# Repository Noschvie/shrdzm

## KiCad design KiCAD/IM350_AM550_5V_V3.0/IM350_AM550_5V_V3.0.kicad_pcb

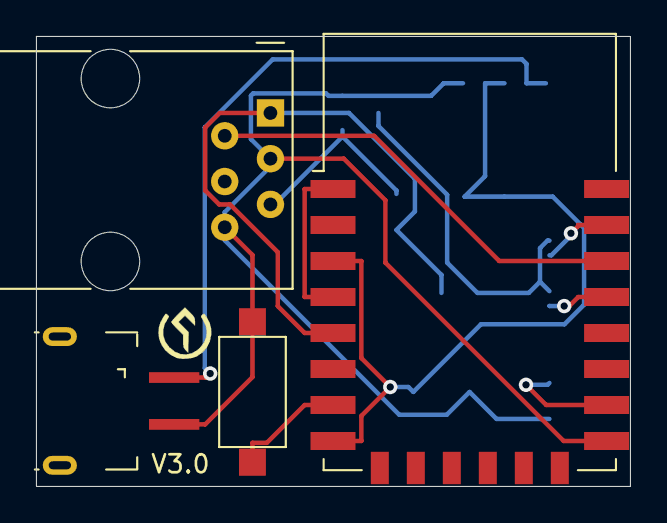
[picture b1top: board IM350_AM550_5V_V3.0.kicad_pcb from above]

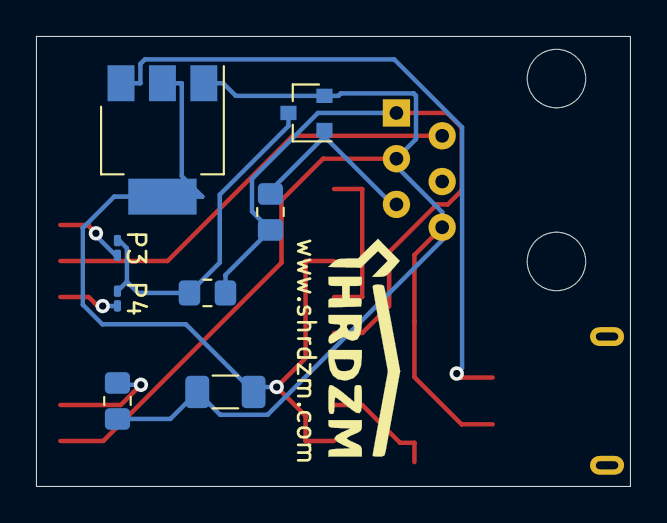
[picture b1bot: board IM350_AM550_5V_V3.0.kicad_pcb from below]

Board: 2 copper layers, 33.0 x 25.0 mm, 14 parts (9 on the bottom side), 12 nets.

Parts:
C1: 22uF; C_1206_3216Metric_Pad1.33x1.80mm_HandSolder
G1: LOGO; SHRDZM Symbol 3x3
G2: LOGO; SHRDZM 12x4
J1: USB_B_Micro_Power; USB_Micro-B_Power
J2: RJ12; RJ12_Amphenol_54601
P3, P4: 2.2k; R_0201_0603Metric_Pad0.64x0.40mm_HandSolder
Q1: BC847; SOT-23
R4, R6: 10k; R_0805_2012Metric_Pad1.20x1.40mm_HandSolder
R5: 2.2k; R_0805_2012Metric_Pad1.20x1.40mm_HandSolder
SW2: SW_Push; SW_SPST_CK_RS282G05A3
U1: AMS1117-3.3; SOT-223-3_TabPin2
U2: ESP-12F; ESP-12E

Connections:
unnamed: C1.1, U1.2, U2.3, U2.8
unnamed: C1.2, J1.5, J2.3, J2.6, Q1.2, R5.2, SW2.2, U1.1, U2.15
unnamed: J1.1, U1.3
unnamed: J2.1, R4.2, R6.2, U2.5
unnamed: J2.2, U2.20
unnamed: J2.5, Q1.1, R6.1
unnamed: P3.1, P4.1, Q1.3, R4.1
unnamed: P3.2, U2.21
unnamed: P4.2, U2.19
unnamed: R5.1, U2.16
unnamed: SW2.1, U2.7
unnamed: U2.1, U2.4

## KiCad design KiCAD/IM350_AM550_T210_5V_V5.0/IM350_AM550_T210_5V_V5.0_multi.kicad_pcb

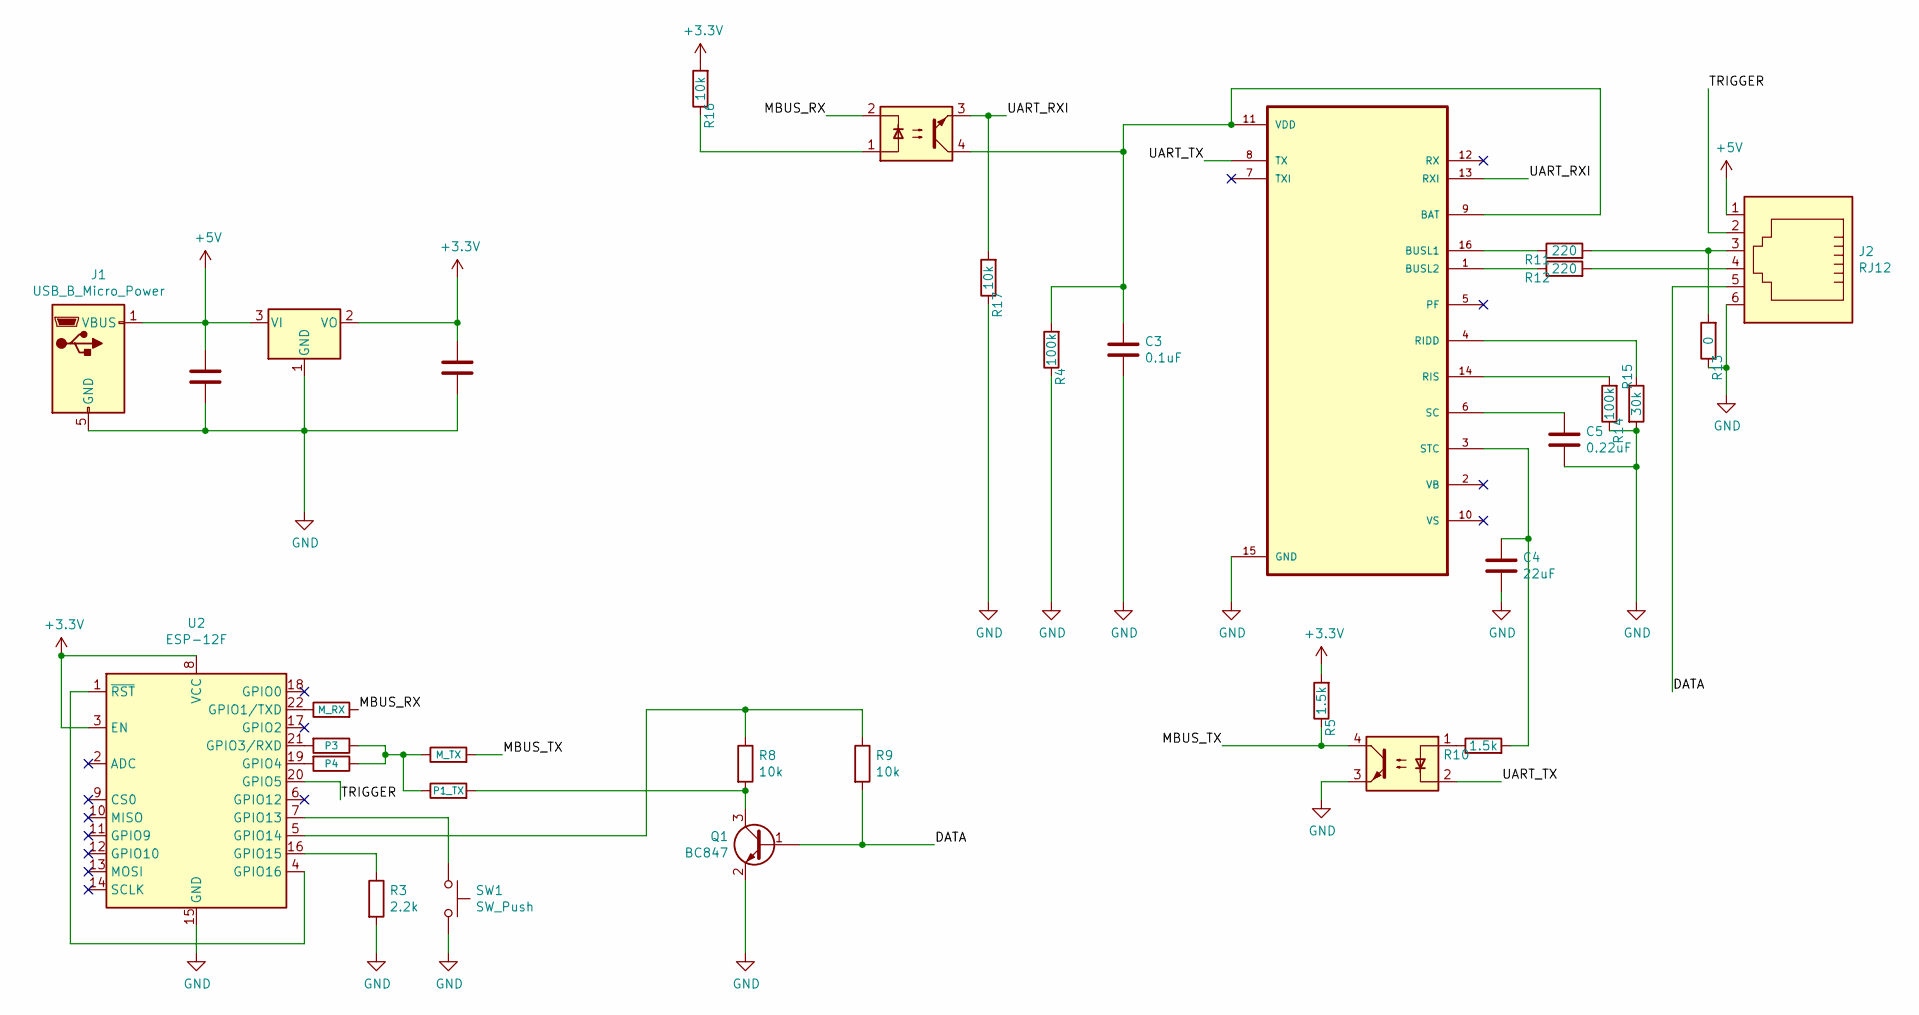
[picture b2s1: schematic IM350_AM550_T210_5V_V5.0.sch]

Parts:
C1, C2, C4: 22uF; C_1206_3216Metric_Pad1.33x1.80mm_HandSolder
C3: 0.1uF; C_1206_3216Metric_Pad1.33x1.80mm_HandSolder
C5: 0.22uF; C_1206_3216Metric_Pad1.33x1.80mm_HandSolder
J1: USB_B_Micro_Power; USB_Micro-B_Power
J2: RJ12; RJ12_Amphenol_54601
Q1: BC847; SOT-23
R1: P3; R_0201_0603Metric_Pad0.64x0.40mm_HandSolder
R2: P4; R_0201_0603Metric_Pad0.64x0.40mm_HandSolder
R3: 2.2k; R_0805_2012Metric_Pad1.20x1.40mm_HandSolder
R4, R14: 100k; R_0805_2012Metric_Pad1.20x1.40mm_HandSolder
R5, R10: 1.5k; R_0805_2012Metric_Pad1.20x1.40mm_HandSolder
R6: M_TX; R_0201_0603Metric_Pad0.64x0.40mm_HandSolder
R7: P1_TX; R_0201_0603Metric_Pad0.64x0.40mm_HandSolder
R8, R9, R16, R17: 10k; R_0805_2012Metric_Pad1.20x1.40mm_HandSolder
R11, R12: 220; R_0805_2012Metric_Pad1.20x1.40mm_HandSolder
R13: 0; R_0201_0603Metric_Pad0.64x0.40mm_HandSolder
R15: 30k; R_0805_2012Metric_Pad1.20x1.40mm_HandSolder
R18: M_RX; R_0201_0603Metric_Pad0.64x0.40mm_HandSolder
SW1: SW_Push; SW_SPST_CK_RS282G05A3
U1: AMS1117-3.3; SOT-223-3_TabPin2
U2: ESP-12F; ESP-12E
U3: TSS721ADR; SOIC127P600X175-16N
U4, U5: EL357NC; SOIC-4_4.55x2.6mm_P1.27mm

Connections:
+3V3: C1.1, R5.2, R16.2, U1.2 (VO), U2.3 (EN), U2.8 (VCC)
+5V: C2.1, J1.1 (VBUS), J2.1, U1.3 (VI)
/DATA: J2.5, Q1.1 (B), R9.2
/MBUS_RX: R18.2, U5.2
/MBUS_TX: R5.1, R6.2, U4.4
/TRIGGER: J2.2, U2.20 (GPIO5)
/UART_RXI: R17.2, U3.13 (RXI), U5.3
/UART_TX: U3.8 (TX), U4.2
GND: C1.2, C2.2, C3.2, C4.2, C5.2, J1.5 (GND), J2.6, Q1.2 (E), R3.2, R4.1, R13.1, R14.1, R15.2, R17.1, SW1.2, U1.1 (GND), U2.15 (GND), U3.15 (GND), U4.3; also elsewhere on the board
unnamed: C3.1, R4.2, U3.9 (BAT), U3.11 (VDD), U5.4
unnamed: C4.1, R10.2, U3.3 (STC)
unnamed: C5.1, U3.6 (SC)
unnamed: J2.4, R12.2
unnamed: Q1.3 (C), R7.2, R8.2
unnamed: R1.1, R2.1, R6.1, R7.1
unnamed: R1.2, U2.21 (GPIO3/RXD)
unnamed: R2.2, U2.19 (GPIO4)
unnamed: R3.1, U2.16 (GPIO15)
unnamed: R8.1, R9.1, U2.5 (GPIO14)
unnamed: R10.1, U4.1
unnamed: R11.1, U3.16 (BUSL1)
unnamed: R12.1, U3.1 (BUSL2)
unnamed: R14.2, U3.14 (RIS)
unnamed: R15.1, U3.4 (RIDD)
unnamed: R16.1, U5.1
unnamed: R18.1, U2.22 (GPIO1/TXD)
unnamed: SW1.1, U2.7 (GPIO13)
unnamed: U2.1 (~RST), U2.4 (GPIO16)

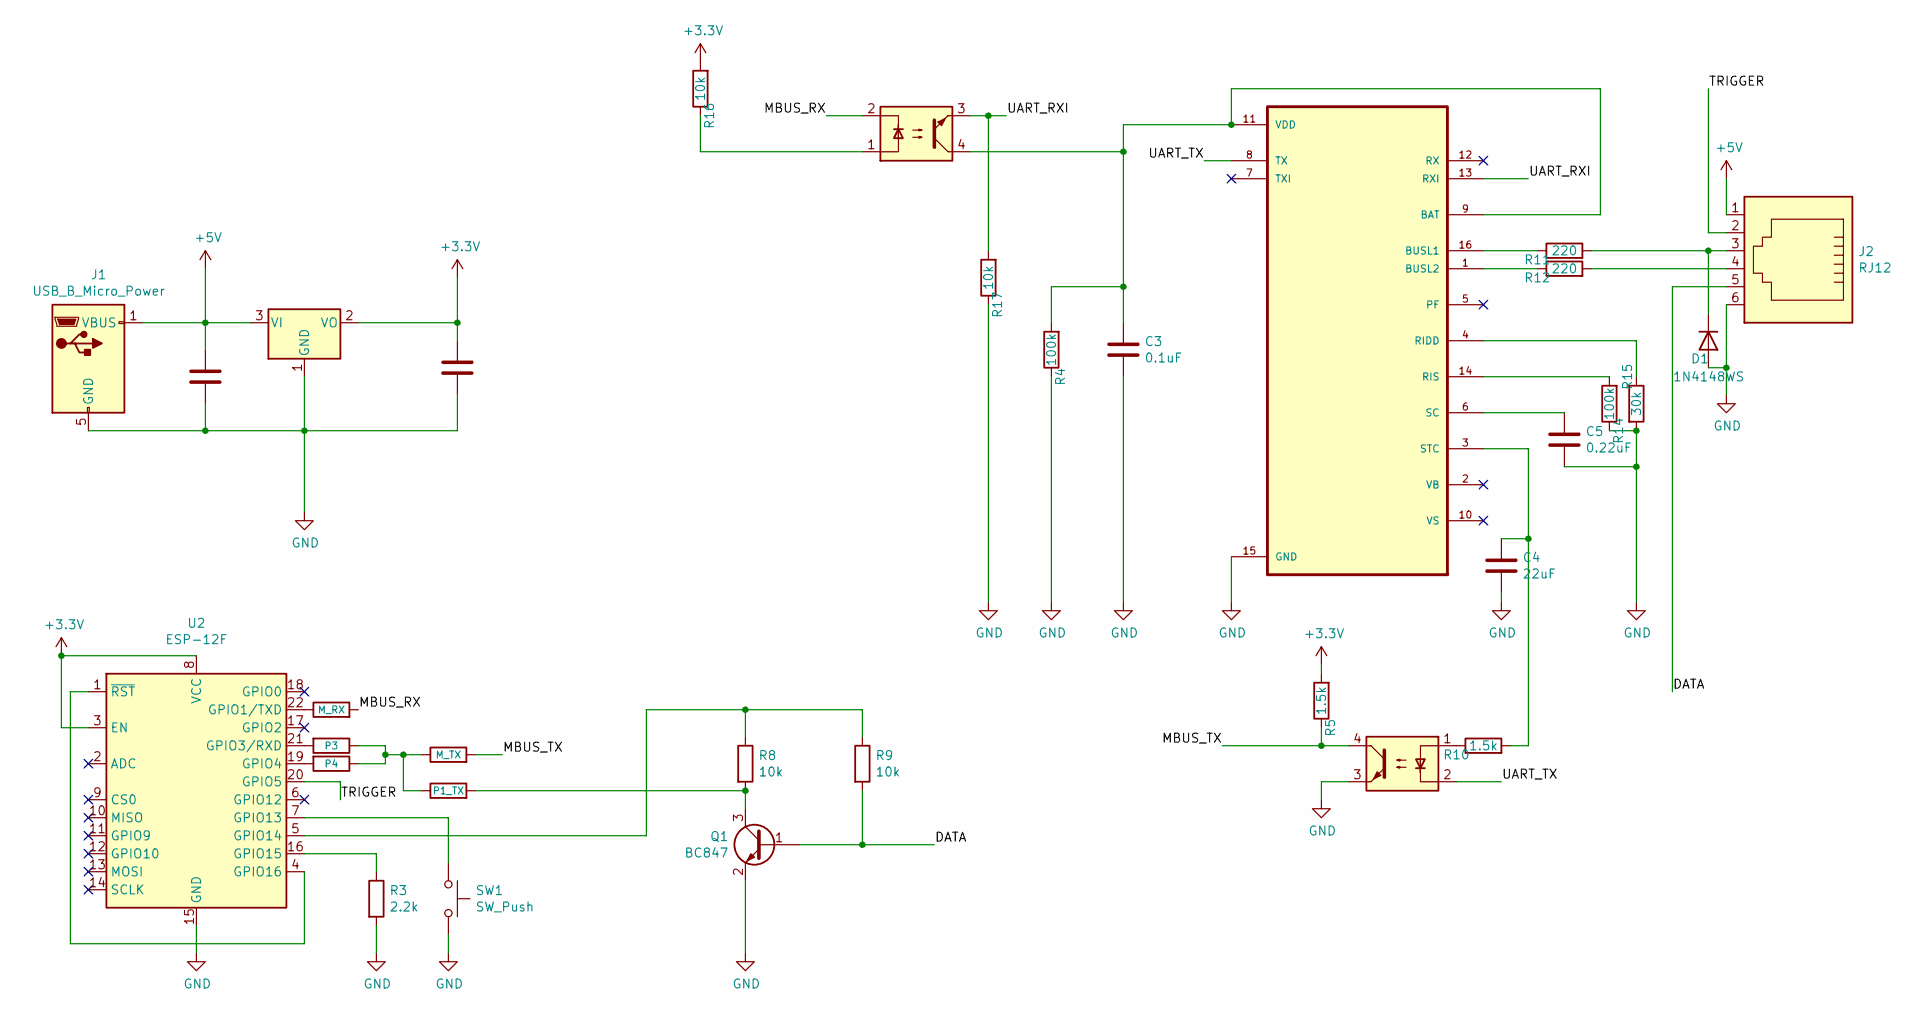
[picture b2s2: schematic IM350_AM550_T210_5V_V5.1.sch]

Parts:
C1, C2, C4: 22uF; C_1206_3216Metric_Pad1.33x1.80mm_HandSolder
C3: 0.1uF; C_1206_3216Metric_Pad1.33x1.80mm_HandSolder
C5: 0.22uF; C_1206_3216Metric_Pad1.33x1.80mm_HandSolder
D1: 1N4148WS; D_SOD-323_HandSoldering
J1: USB_B_Micro_Power; USB_Micro-B_Power
J2: RJ12; RJ12_Amphenol_54601
Q1: BC847; SOT-23
R1: P3; R_0201_0603Metric_Pad0.64x0.40mm_HandSolder
R2: P4; R_0201_0603Metric_Pad0.64x0.40mm_HandSolder
R3: 2.2k; R_0805_2012Metric_Pad1.20x1.40mm_HandSolder
R4, R14: 100k; R_0805_2012Metric_Pad1.20x1.40mm_HandSolder
R5, R10: 1.5k; R_0805_2012Metric_Pad1.20x1.40mm_HandSolder
R6: M_TX; R_0201_0603Metric_Pad0.64x0.40mm_HandSolder
R7: P1_TX; R_0201_0603Metric_Pad0.64x0.40mm_HandSolder
R8, R9, R16, R17: 10k; R_0805_2012Metric_Pad1.20x1.40mm_HandSolder
R11, R12: 220; R_0805_2012Metric_Pad1.20x1.40mm_HandSolder
R15: 30k; R_0805_2012Metric_Pad1.20x1.40mm_HandSolder
R18: M_RX; R_0201_0603Metric_Pad0.64x0.40mm_HandSolder
SW1: SW_Push; SW_SPST_CK_RS282G05A3
U1: AMS1117-3.3; SOT-223-3_TabPin2
U2: ESP-12F; ESP-12E
U3: TSS721ADR; SOIC127P600X175-16N
U4, U5: EL357NC; SOIC-4_4.55x2.6mm_P1.27mm

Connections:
+3V3: C1.1, R5.2, R16.2, U1.2 (VO), U2.3 (EN), U2.8 (VCC)
+5V: C2.1, J1.1 (VBUS), J2.1, U1.3 (VI)
/DATA: J2.5, Q1.1 (B), R9.2
/MBUS_RX: R18.2, U5.2
/MBUS_TX: R5.1, R6.2, U4.4
/TRIGGER: J2.2, U2.20 (GPIO5)
/UART_RXI: R17.2, U3.13 (RXI), U5.3
/UART_TX: U3.8 (TX), U4.2
GND: C1.2, C2.2, C3.2, C4.2, C5.2, D1.2 (A), J1.5 (GND), J2.6, Q1.2 (E), R3.2, R4.1, R14.1, R15.2, R17.1, SW1.2, U1.1 (GND), U2.15 (GND), U3.15 (GND), U4.3; also elsewhere on the board
unnamed: C3.1, R4.2, U3.9 (BAT), U3.11 (VDD), U5.4
unnamed: C4.1, R10.2, U3.3 (STC)
unnamed: C5.1, U3.6 (SC)
unnamed: J2.4, R12.2
unnamed: Q1.3 (C), R7.2, R8.2
unnamed: R1.1, R2.1, R6.1, R7.1
unnamed: R1.2, U2.21 (GPIO3/RXD)
unnamed: R2.2, U2.19 (GPIO4)
unnamed: R3.1, U2.16 (GPIO15)
unnamed: R8.1, R9.1, U2.5 (GPIO14)
unnamed: R10.1, U4.1
unnamed: R11.1, U3.16 (BUSL1)
unnamed: R12.1, U3.1 (BUSL2)
unnamed: R14.2, U3.14 (RIS)
unnamed: R15.1, U3.4 (RIDD)
unnamed: R16.1, U5.1
unnamed: R18.1, U2.22 (GPIO1/TXD)
unnamed: SW1.1, U2.7 (GPIO13)
unnamed: U2.1 (~RST), U2.4 (GPIO16)

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
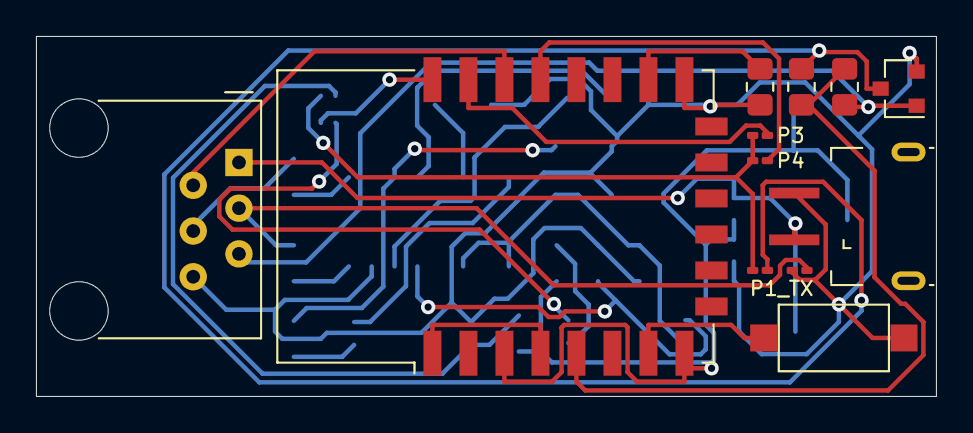
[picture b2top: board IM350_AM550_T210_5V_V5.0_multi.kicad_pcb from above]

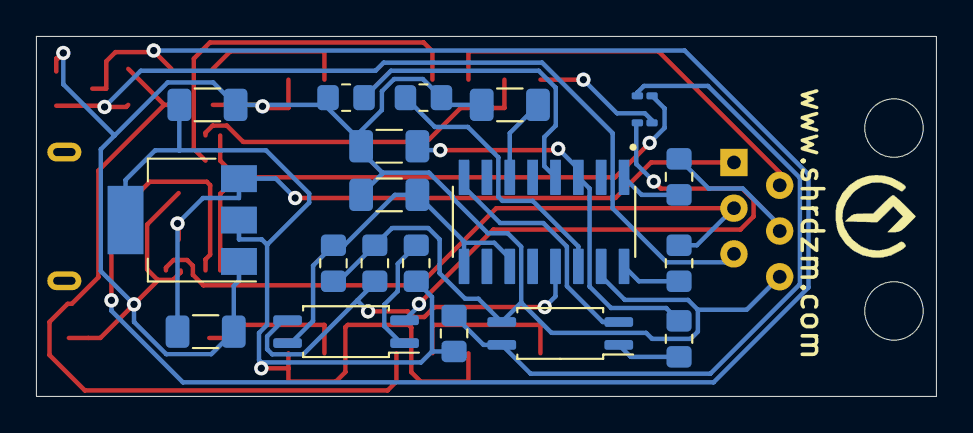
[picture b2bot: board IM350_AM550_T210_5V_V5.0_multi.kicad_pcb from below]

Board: 2 copper layers, 50.0 x 20.0 mm, 33 parts (21 on the bottom side), 29 nets.

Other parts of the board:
G1: LOGO; SHRDZM Symbol 5x5

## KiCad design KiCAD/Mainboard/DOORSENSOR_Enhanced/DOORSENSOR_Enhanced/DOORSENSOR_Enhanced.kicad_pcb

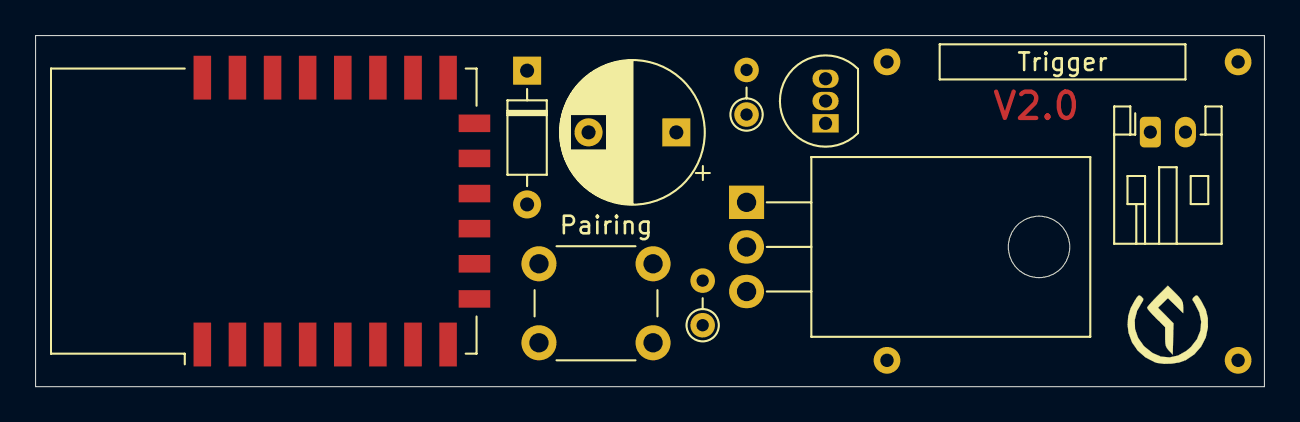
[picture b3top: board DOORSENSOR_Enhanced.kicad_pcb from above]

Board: 2 copper layers, 70.0 x 20.0 mm, 11 parts (1 on the bottom side), 10 nets, no tracks yet.

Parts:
C1: 33uF; CP_Radial_D8.0mm_P5.00mm
D1: 1N4148; D_DO-35_SOD27_P7.62mm_Horizontal
J1: Power; JST_PH_S2B-PH-K_1x02_P2.00mm_Horizontal
Q1: 2N2222; TO-92_Inline
Q2: NDP6020P; TO-220-3_Horizontal_TabDown
R1: 10k; R_Axial_DIN0204_L3.6mm_D1.6mm_P2.54mm_Vertical
R2: 1k; R_Axial_DIN0204_L3.6mm_D1.6mm_P2.54mm_Vertical
SW1: Trigger; Magnetic Reed Relay
SW2: Pairing; SW_PUSH_6mm
SW3: Open/Close; Magnetic Reed Relay
U1: ESP-12F; ESP-12E

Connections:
+3V3: J1.2, Q2.3, R2.1, SW1.1
GND: C1.2, J1.1, Q1.1, SW2.2, SW3.2, U1.15, U1.16
unnamed: C1.1, D1.1, R1.2, SW1.2
unnamed: D1.2, U1.5
unnamed: Q1.2, R1.1
unnamed: Q1.3, Q2.1, R2.2
unnamed: Q2.2, U1.3, U1.8
unnamed: SW2.1, U1.7
unnamed: SW3.1, U1.20
unnamed: U1.1, U1.4
